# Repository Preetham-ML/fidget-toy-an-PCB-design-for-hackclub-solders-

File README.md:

# Fidget Dashboard

A handheld fidget toy PCB built for Hack Club's **Solder** program. It combines manual button-triggered LEDs with a light-sensing (photoresistor) circuit that turns LEDs on automatically depending on ambient light.

## What it does
- **Manual circuit:** Two push buttons (SW1, SW2) feed into a pair of 2N3904 transistors (Q1, Q2), which switch power to an LED (D1) when pressed.
- **Light-sensing circuit:** A GL5528 photoresistor (R7) and a 10kΩ potentiometer (RV1) form a light-dependent voltage divider. This feeds a third 2N3904 (Q3), which switches a pair of LEDs (D2, D3) on or off automatically as ambient light changes — the potentiometer lets you tune the sensitivity/threshold.

Power comes from a battery cell behind VCC/GND rails feeding both halves of the circuit.

## Bill of Materials

| Part                  | Reference  | Qty | 
| --- | --- | --- |
| 2N3904 NPN transistor | Q1, Q2, Q3 | 3 | 
| 220Ω resistor         | R3, R5, R6 | 3 | 
| 4.7kΩ resistor        | R1, R2, R4 | 3 |
| 10kΩ potentiometer    | RV1 | 1 |
| GL5528 photoresistor  | R7 | 1 |
| 5mm LED               | D1, D2, D3 | 3 |
| 6mm push button       | SW1, SW2 | 2 |
| CR2032 battery cell   | BT1 , BT2 | 2 | 

## Screenshots

- [ 
] Schematic screenshot    
- [
 ] PCB layout screenshot (front + back if double sided)
- [
 ] 3D render screenshot

## Files in this repo
all the files of my fidget dashboard are upload in repo 
## Slack username
preetham ml
## Notes / Reflections
> - This my first every PCB project. I had to learn all the basic electronics how to use kicad but its kinda fun knowning no errors looking at 3d model. i like the feel. yep it took me 5 days from learning basic electronics to design my first pcb (btw its scecond before truning down like 5-10 desings, first was battery resistor and an bulb.)
> - ahhh The reason select this design cause every one loves when light when darks up (atleast for me ) and also wanted to be fun toy so i add the two push button led.
> - THE tricky part was the wiring its alone took 2+days its hell.
> - what i learn - was like every thing is new to me  but to undo the trickyness of wiring make pcb desing as similar to schematics

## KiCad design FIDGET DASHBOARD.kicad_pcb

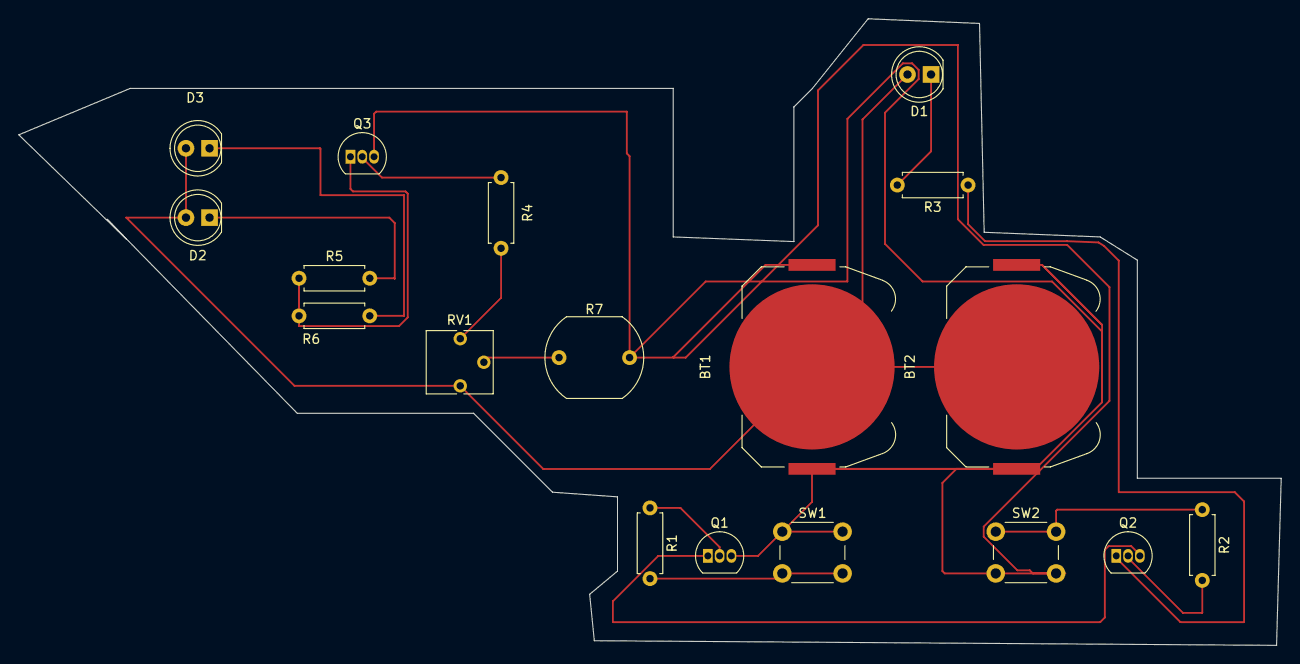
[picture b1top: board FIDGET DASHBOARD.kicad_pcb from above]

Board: 2 copper layers, 136.0 x 67.5 mm, 18 parts (0 on the bottom side), 15 nets.

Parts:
BT1, BT2: Battery_Cell; BatteryHolder_Keystone_3034_1x20mm
D1, D2, D3: LED; LED_D5.0mm
Q1, Q2, Q3: 2N3904; TO-92_Inline
R1, R2, R4: 4.7k; R_Axial_DIN0207_L6.3mm_D2.5mm_P7.62mm_Horizontal
R3, R5, R6: 220; R_Axial_DIN0207_L6.3mm_D2.5mm_P7.62mm_Horizontal
R7: LDR03; R_LDR_10x8.5mm_P7.6mm_Vertical
RV1: 10k; Potentiometer_Vishay_T73YP_Vertical
SW1, SW2: SW_Push; SW_PUSH_6mm

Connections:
/GND: BT1.2 (-), BT2.2 (-), D1.2 (A), D2.2 (A), D3.2 (A), RV1.1
/VCC: BT1.1 (+), BT2.1 (+), Q1.3 (C), Q3.3 (C), R7.2, SW1.1, SW2.2
unnamed: D1.1 (K), R3.2
unnamed: D2.1 (K), R5.2
unnamed: D3.1 (K), R6.2
unnamed: Q1.2 (B), R1.1
unnamed: Q1.1 (E), Q2.3 (C)
unnamed: Q2.2 (B), R2.2
unnamed: Q2.1 (E), R3.1
unnamed: Q3.2 (B), R4.1
unnamed: Q3.1 (E), R5.1, R6.1
unnamed: R1.2, SW1.2
unnamed: R2.1, SW2.1
unnamed: R4.2, RV1.3
unnamed: R7.1, RV1.2

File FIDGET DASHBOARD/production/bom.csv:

Designator,Footprint,Quantity,Value,LCSC Part #
"BT1, BT2",BatteryHolder_Keystone_3034_1x20mm,2,Battery_Cell,
"D1, D2, D3",LED_D5.0mm,3,LED,
"Q1, Q2, Q3",TO-92_Inline,3,2N3904,
"R1, R2, R4",R_Axial_DIN0207_L6.3mm_D2.5mm_P7.62mm_Horizontal,3,4.7k,
"R3, R5, R6",R_Axial_DIN0207_L6.3mm_D2.5mm_P7.62mm_Horizontal,3,220,
R7,R_LDR_10x8.5mm_P7.6mm_Vertical,1,LDR03,
RV1,Potentiometer_Vishay_T73YP_Vertical,1,10k,
"SW1, SW2",SW_PUSH_6mm,2,SW_Push,

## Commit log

2026-06-18 Revise README for Fidget Dashboard project
    Updated the README to provide a detailed overview of the Fidget Dashboard project, including its functionality, bill of materials, screenshots, and personal reflections on the design process.
2026-06-18 Fix formatting in Bill of Materials table
